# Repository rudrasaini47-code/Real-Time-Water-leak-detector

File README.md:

# Real Time Water Leak Detector
 
> **Smart water pipeline leak detection system with automatic valve shutoff, real-time web dashboard, and WiFi monitoring — built with Arduino Uno, NodeMCU ESP8266, and YF-S201 flow sensors.**
 
---
 
##  Demo
 
```
Flow IN: 14.20 L/min  |  Flow OUT: 11.60 L/min  |  Diff: 2.60 L/min  →   LEAK DETECTED → True
```
 
Live dashboard updates every 2 seconds. Leak triggers browser notification + sound alert + automatic valve shutoff within 3 seconds of detection.
 
---
 
##  Features
 
- **Real-time flow monitoring** — measures Flow IN and Flow OUT simultaneously using YF-S201 Hall-effect sensors
- **Intelligent leak detection** — compares flow difference mathematically (no moisture sensor needed)
- **False alarm prevention** — requires 3 consecutive seconds of sustained difference before triggering
- **Automatic valve shutoff** — 12V solenoid valve closes instantly when leak is confirmed
- **WiFi dashboard** — live web UI accessible from any browser on the same network
- **Multi-alert system** — in-app toast, browser push notification, and sound alert on leak
- **No cloud needed** — ESP8266 hosts its own API endpoint on local WiFi
- **Works with hotspot** — connect ESP8266 to mobile hotspot for portable use
---
 
##  Hardware Required
 
| Component | Quantity | Notes |
|---|---|---|
| Arduino Uno (R3) | 1 | Any revision |
| NodeMCU v3.0 (ESP8266) | 1 | Has onboard USB — easiest to flash |
| YF-S201 Flow Sensor | 2 | One inlet, one outlet |
| 1kΩ Resistor | 1 | Voltage divider |
| 2kΩ Resistor | 1 | Voltage divider (or 2× 1kΩ in series) |
| Breadboard + Jumper Wires | — | Male-to-male and male-to-female |

##  Wiring
 
### Arduino Uno Pin Connections
| Arduino Pin | Connected To |
|---|---|
| `2` (Digital) | YF-S201 Flow IN signal (yellow wire) |
| `3` (Digital) | YF-S201 Flow OUT signal (yellow wire) |
| `TX` (pin 1) | NodeMCU RX via voltage divider |
| `RX` (pin 0) | NodeMCU TX (direct) |
| `5V` | Both YF-S201 VCC (red wires) + Relay VCC |
| `3.3V` | NodeMCU 3V3 pin |
| `GND` | All component GNDs (shared) |
 
### NodeMCU v3.0 Pin Connections
 
| NodeMCU Pin | Connected To |
|---|---|
| `3V3` | Arduino 3.3V |
| `GND` | Arduino GND (shared) |
| `D9 / RX` | Arduino TX (pin 1) via voltage divider |
| `D10 / TX` | Arduino RX (pin 0) direct |
 
> All other NodeMCU pins are left unconnected.
 
### Voltage Divider (mandatory — protects NodeMCU RX from 5V)
 
```
Arduino TX (pin 1) ──[1kΩ]──┬──── NodeMCU RX (D9)
                             │
                           [2kΩ]
                             │
                            GND
 
Output voltage: 5V × (2kΩ / 3kΩ) = 3.33V ✓
```
 
##  File Structure
 
```
FlowWatch
│
├── arduino_flowwatch.ino     ← Upload to Arduino Uno
├── esp8266_flowwatch.ino     ← Upload to NodeMCU ESP8266
├── flow-monitor.html         ← Open in browser for dashboard
└── README.md
```

## PCB Specifications
 
- **Layers:** 2 (F.Cu / B.Cu)
- **Thickness:** 1.6 mm
- **Mounting:** 4x 2.5mm mounting holes
- **Connectors:** 6x 3.5mm screw terminals (Degson DG250 series)
- **Design tool:** KiCad

## Files
 
- `RealTimeWaterLeak.kicad_sch` — Schematic
- `RealTimeWaterLeak.kicad_pcb` — PCB layout
 
---
 
##  Setup
 
### Step 1 — Configure WiFi credentials
 
Open `esp8266_flowwatch.ino` and set your WiFi name and password:
 
```cpp
const char* WIFI_SSID     = "Your_WiFi_Or_Hotspot_Name";
const char* WIFI_PASSWORD = "yourpassword";
```
 
> **Note:** ESP8266 only supports 2.4GHz WiFi. If using Android hotspot, force it to 2.4GHz in hotspot settings.

### Step 2 — Upload Arduino code
 
1. **Disconnect NodeMCU TX/RX wires** from Arduino pins 0 and 1
2. Connect Arduino to laptop via USB
3. Arduino IDE → Tools → Board → **Arduino Uno**
4. Upload `arduino_flowwatch.ino`
5. Open Serial Monitor at **9600 baud** — verify output looks like:
```
   IN:0.00,OUT:0.00,LEAK:0,VALVE:1,DIFF:0.00
```
6. Close Serial Monitor → reconnect NodeMCU TX/RX wires
### Step 3 — Upload ESP8266 code
 
1. Connect **NodeMCU** to laptop via USB (Arduino disconnected)
2. Arduino IDE → Tools → Board → **NodeMCU 1.0 (ESP-12E Module)**
3. Tools → Upload Speed → **115200**
4. Upload `esp8266_flowwatch.ino`
5. LED blinks while connecting to WiFi, goes solid when connected
### Step 4 — Find NodeMCU IP address
 
- **Mobile hotspot:** Check connected devices list in your hotspot settings — look for "espressif"
- **Home router:** Open router admin page → connected devices → find "ESP8266"
- **Verify:** Open `http://<ESP_IP>/` in browser — status page should load with live readings
### Step 5 — Open dashboard
 
1. Open `flow-monitor.html` in Chrome or Edge
2. Enter API URL: `http://<ESP_IP>/api/flow-data`
3. Click **▶ Start Polling**
4. Allow browser notification permission
5. All 5 cards update in real time 
---
 
##  How Leak Detection Works
 
```
Every 1 second:
  flowDiff = flowIn − flowOut
 
  if flowDiff < 2.0  →  Normal, reset counter
  if flowDiff ≥ 2.0  →  Increment confirmation counter
  if counter ≥ 3     →  LEAK CONFIRMED
                           → dashboard alerts fire
                           → browser notification sent
                           → sound alert plays
 
Press reset button (D6) after fixing leak → valve reopens
```
 
The 3-second confirmation window prevents false alarms from sensor jitter when taps open/close suddenly.
 
---
 
##  API Reference
 
The NodeMCU hosts a JSON REST API on port 80.
 
### `GET /api/flow-data`
 
```json
{
  "flow_in": 14.20,
  "flow_out": 11.60,
  "flow_diff": 2.60,
  "leak": 1,
  "valve_open": 0,
  "uptime_s": 3420,
  "has_data": true,
  "stale": false
}
```
 
| Field | Type | Description |
|---|---|---|
| `flow_in` | float | Inlet flow rate in L/min |
| `flow_out` | float | Outlet flow rate in L/min |
| `flow_diff` | float | Difference (flow_in − flow_out) |
| `leak` | int | 0 = normal, 1 = leak detected |
| `uptime_s` | int | ESP8266 uptime in seconds |
| `has_data` | bool | False until first Arduino reading received |
| `stale` | bool | True if no update received in 10+ seconds |
 
### `GET /`
 
Human-readable status page. Auto-refreshes every 2 seconds.
 
---
 
##  Configuration
 
Adjustable constants in `arduino_flowwatch.ino`:
 
```cpp
const float LEAK_THRESHOLD    = 2.0;   // L/min difference to trigger alert
const int   CONFIRM_COUNT     = 3;     // Consecutive detections before confirming
const float CALIBRATION_FACTOR = 7.5;  // YF-S201: pulses/sec per L/min
const unsigned long SEND_INTERVAL = 2000;  // How often to send data to ESP (ms)
```
 
**Tuning tips:**
- Too many false alarms → increase `LEAK_THRESHOLD` to 3.0 or `CONFIRM_COUNT` to 5
- Missing real leaks → decrease `LEAK_THRESHOLD` to 1.0 or 1.5
- Readings seem off → adjust `CALIBRATION_FACTOR` (valid range: 4.5 – 8.5 for YF-S201)
---
 
##  Important Notes
 
### Upload rule
**Always disconnect NodeMCU TX/RX wires before uploading to Arduino.** Arduino Uno shares its only serial port (pins 0/1) with USB. Reconnect after upload.
 
### Power
- Arduino powered by USB (any 5V phone charger or laptop)
- NodeMCU powered from Arduino 3.3V pin — **do not connect NodeMCU USB and Arduino 3.3V simultaneously**

### Network
The device running the dashboard must be on the **same WiFi/hotspot** as the NodeMCU. The NodeMCU IP may change after power cycles — set a static DHCP lease in your router to fix it permanently.
 
---
 
##  Troubleshooting
 
| Problem | Cause | Fix |
|---|---|---|
| Dashboard shows all zeros | Serial Monitor open | Close Serial Monitor — it conflicts with ESP communication |
| Dashboard shows all zeros | Two power sources on NodeMCU | Remove USB from NodeMCU — power only from Arduino 3.3V |
| Flow always reads 0.00 | Wrong interrupt pins | YF-S201 signal must go to pin **2** and pin **3** on Uno |
| ESP not connecting to WiFi | Wrong credentials or 5GHz | Double-check SSID/password. Force Android hotspot to 2.4GHz |
| ESP broadcasting own WiFi | Failed to join network | Same as above — ESP falls back to AP mode on failure |
| Upload fails | NodeMCU TX/RX still connected | Disconnect pins 0 and 1 from NodeMCU before uploading |
| False leak alerts | Sensor jitter | Increase `LEAK_THRESHOLD` to 3.0 or `CONFIRM_COUNT` to 5 |
| Random ESP resets | Power instability | Add 100µF capacitor between NodeMCU 3V3 and GND |
 
---

## Built With
 
- **Arduino Uno** — sensor reading, flow calculation, valve control
- **NodeMCU ESP8266** — WiFi connectivity, JSON API server
- **YF-S201** — Hall-effect pulse flow sensors
- **Arduino IDE** — firmware development
- **Chart.js** — real-time flow history chart in dashboard
- **Vanilla HTML/CSS/JS** — zero-dependency web dashboard
---

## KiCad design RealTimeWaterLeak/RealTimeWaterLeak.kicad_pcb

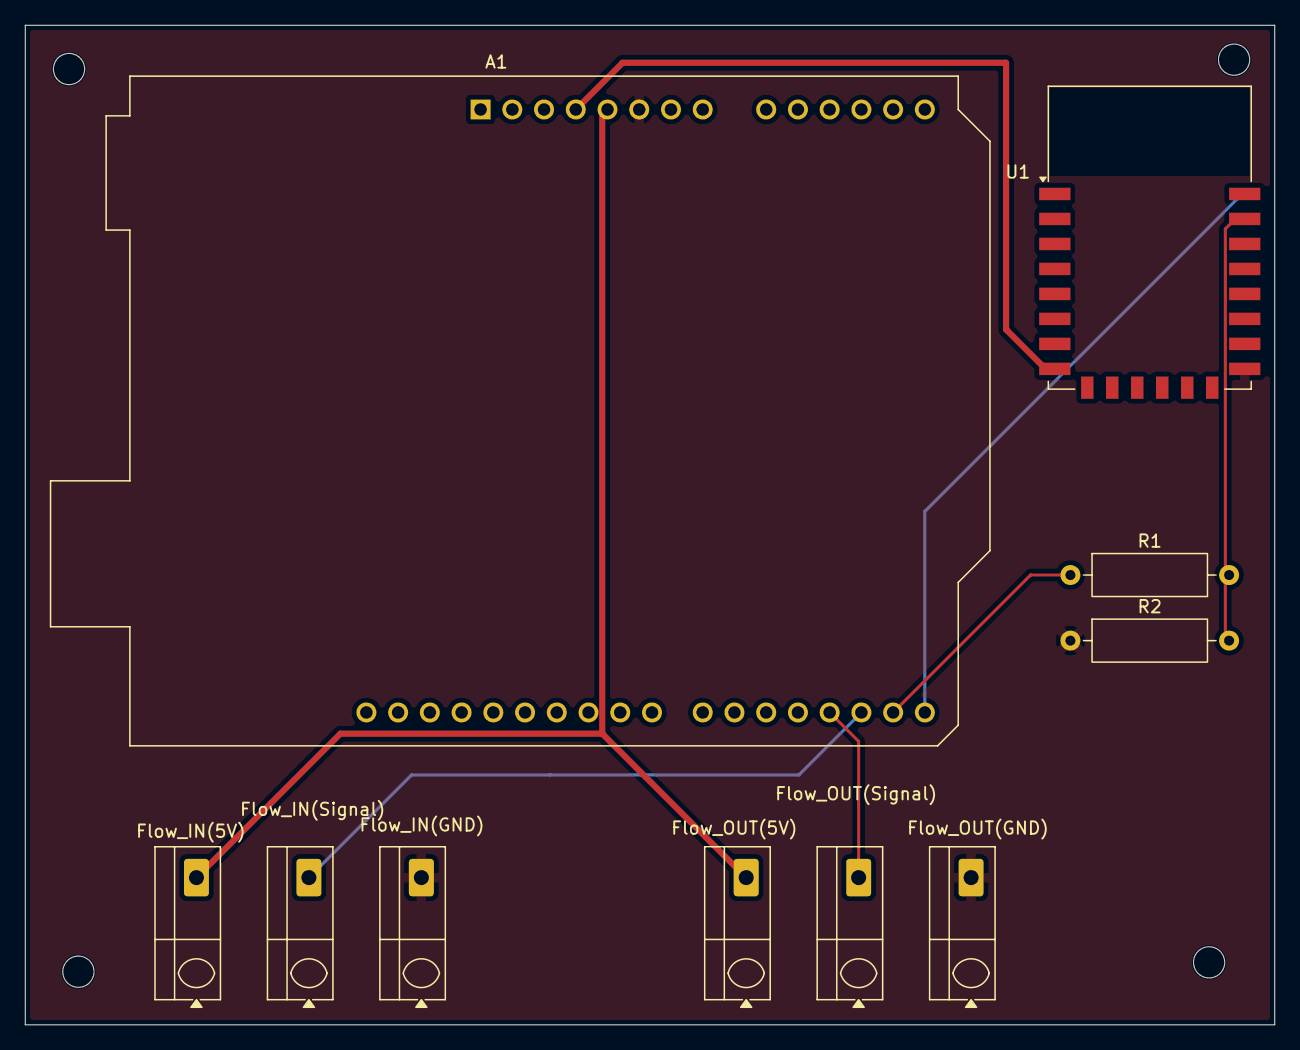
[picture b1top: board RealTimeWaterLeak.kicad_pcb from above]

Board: 2 copper layers, 100.0 x 80.0 mm, 10 parts (0 on the bottom side), 8 nets.

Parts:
A1: Arduino_UNO_R3
Flow_IN(5V): Screw_Terminal_01x01; TerminalBlock_Degson_DG250-3.5-01P_1x01_P3.50mm_45Degree
Flow_IN(GND): Screw_Terminal_01x01; TerminalBlock_Degson_DG250-3.5-01P_1x01_P3.50mm_45Degree
Flow_IN(Signal): Screw_Terminal_01x01; TerminalBlock_Degson_DG250-3.5-01P_1x01_P3.50mm_45Degree
Flow_OUT(5V): Screw_Terminal_01x01; TerminalBlock_Degson_DG250-3.5-01P_1x01_P3.50mm_45Degree
Flow_OUT(GND): Screw_Terminal_01x01; TerminalBlock_Degson_DG250-3.5-01P_1x01_P3.50mm_45Degree
Flow_OUT(Signal): Screw_Terminal_01x01; TerminalBlock_Degson_DG250-3.5-01P_1x01_P3.50mm_45Degree
R1: 1 kohm; R_Axial_DIN0309_L9.0mm_D3.2mm_P12.70mm_Horizontal
R2: 2 kohm; R_Axial_DIN0309_L9.0mm_D3.2mm_P12.70mm_Horizontal
U1: ESP-12E

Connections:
+3.3V: A1.4 (3V3), U1.8 (VCC)
+5V: A1.5 (+5V), Flow_IN(5V).1 (Pin_1_1), Flow_OUT(5V).1 (Pin_1_1)
GND: A1.6 (GND), Flow_IN(GND).1 (Pin_1_1), Flow_OUT(GND).1 (Pin_1_1), R2.1, U1.15 (GND)
unnamed: A1.15 (D0/RX), U1.22 (GPIO1/TXD)
unnamed: A1.16 (D1/TX), R1.1
unnamed: A1.17 (D2), Flow_IN(Signal).1 (Pin_1_1)
unnamed: A1.18 (D3), Flow_OUT(Signal).1 (Pin_1_1)
unnamed: R1.2, R2.2, U1.21 (GPIO3/RXD)

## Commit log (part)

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2026-04-09 Create Web-page
